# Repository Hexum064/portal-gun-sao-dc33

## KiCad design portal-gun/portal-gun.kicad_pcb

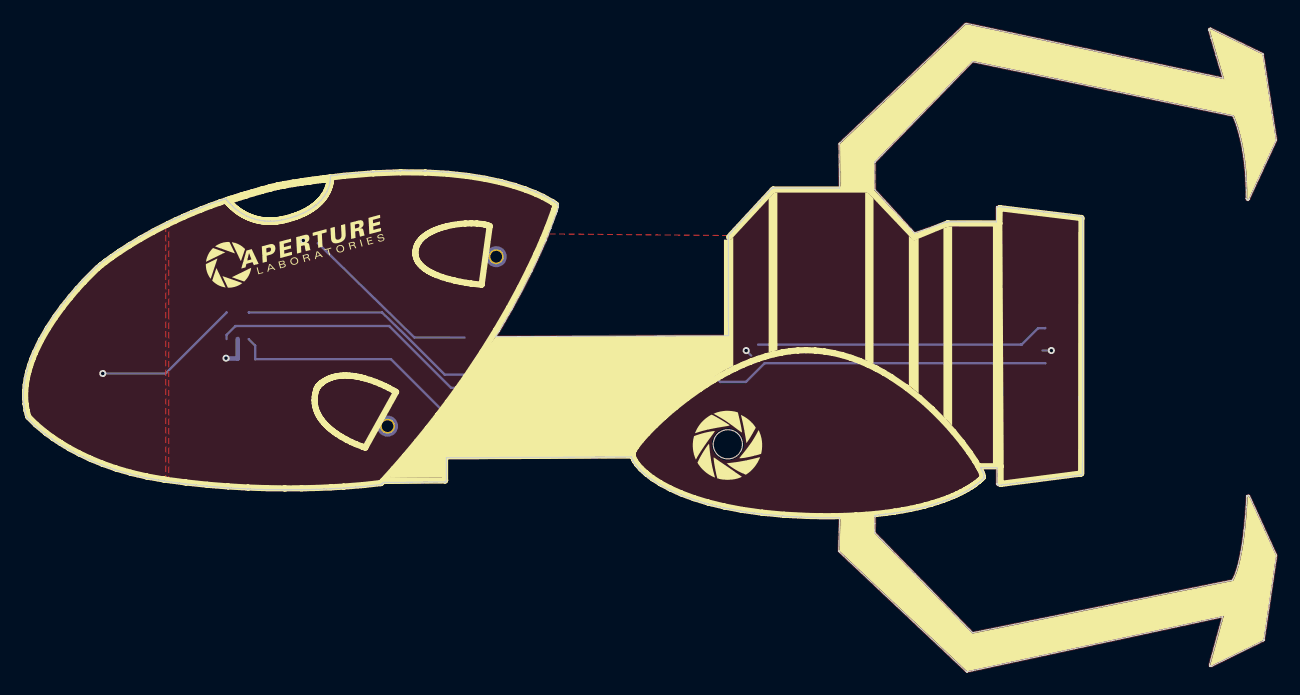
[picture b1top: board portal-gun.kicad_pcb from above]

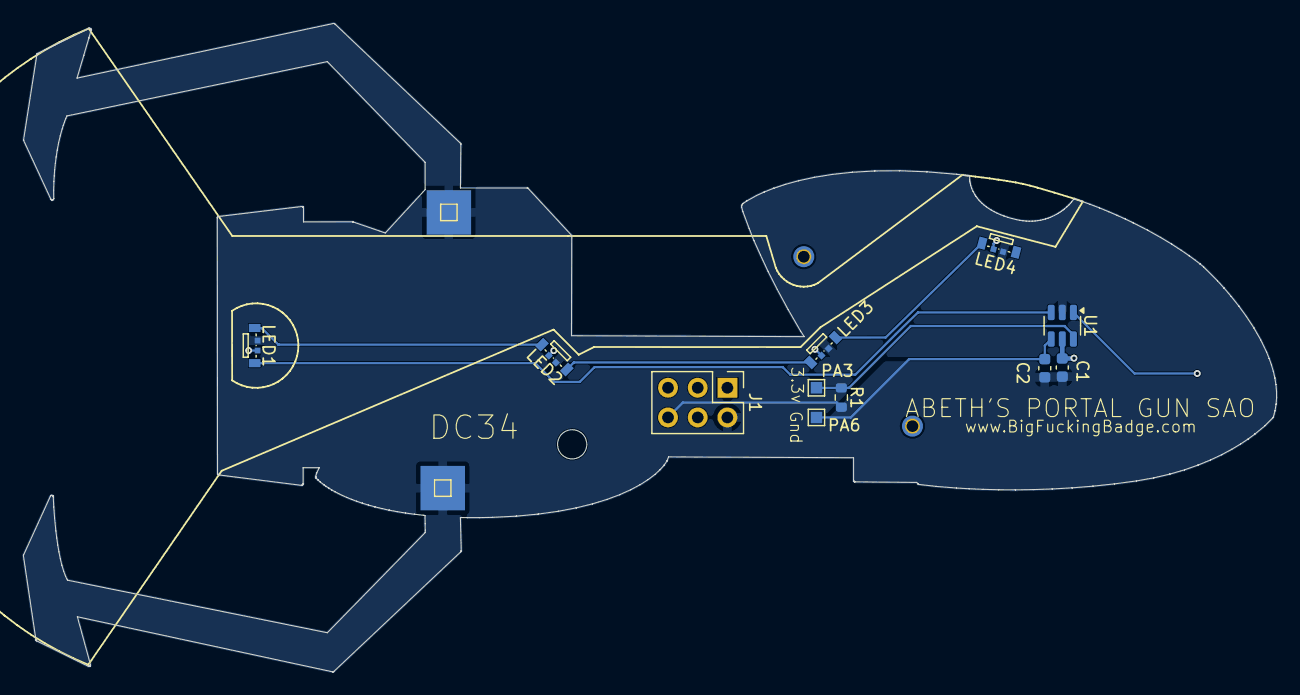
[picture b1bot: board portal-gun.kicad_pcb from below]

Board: 2 copper layers, 107.2 x 55.5 mm, 11 parts (11 on the bottom side), 9 nets.

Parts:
C1: 10nF; C_0603_1608Metric
C2: 470pF; C_0603_1608Metric
J1: SAO; PinHeader_2x03_P2.54mm_Vertical
LED1, LED2, LED3, LED4: LED-SMD_4P_SK6812D-EC3210R
PA3: PA3; TestPoint_Pad_1.0x1.0mm
PA6: PA6; TestPoint_Pad_1.0x1.0mm
R1: R_Small; R_0603_1608Metric
U1: SOT-23-6

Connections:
GND: C1.2, C2.2, J1.2, LED1.1 (GND), LED2.1 (GND), LED3.1 (GND), LED4.1 (GND), U1.2 (GND)
unnamed: J1.6, R1.1
unnamed: LED1.3 (DIN), U1.3 (PA5)
unnamed: LED1.2 (DOUT), LED2.3 (DIN)
unnamed: LED2.2 (DOUT), LED3.3 (DIN)
unnamed: LED3.2 (DOUT), LED4.3 (DIN)
unnamed: PA3.1 (1_1), R1.2, U1.6 (PA3)
unnamed: C2.1, PA6.1 (1_1), U1.4 (PA6/7)
VDD: C1.1, J1.1, LED1.4 (VDD), LED2.4 (VDD), LED3.4 (VDD), LED4.4 (VDD), U1.5 (VDD)

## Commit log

2025-03-04 inital commit
2025-03-04 added in pdk libs
2025-03-05 implemented tone on startup and button
2025-03-21 updating make
2025-03-22 fast forward
2025-03-22 moving code into separate repo
2025-03-24 updated design with front fill as vcc
2025-04-02 change over to different LED and fix design
2025-04-18 final proto updates
2026-04-17 added res to pin 6 for output
2026-04-17 cleanup and new plexi cutouts
